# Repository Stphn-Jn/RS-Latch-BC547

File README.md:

R   S   Q   OUTPUT
0   0   0     0
1   0   0     1
1   1   0     0
0   1   0     0
0   0   0     0
1   1   1     0
0   1   1     0

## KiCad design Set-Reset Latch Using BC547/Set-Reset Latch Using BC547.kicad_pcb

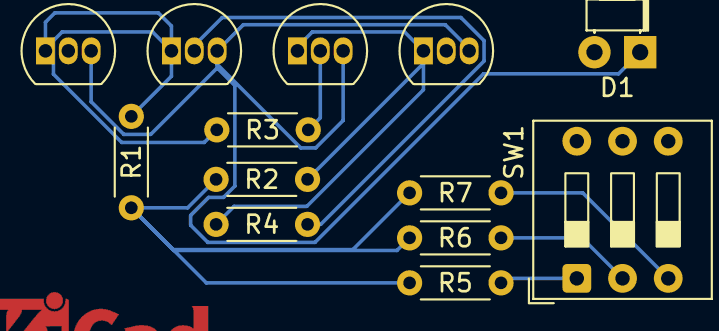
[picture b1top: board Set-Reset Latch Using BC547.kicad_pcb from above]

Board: 2 copper layers, 13 parts (0 on the bottom side), 11 nets.

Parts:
D1: LED; LED_D1.8mm_W1.8mm_H2.4mm_Horizontal_O1.27mm_Z4.9mm
Q1, Q2, Q3, Q4: BC547; TO-92_Inline
R1, R2, R3, R4, R5, R6, R7: 1K; R_Axial_DIN0204_L3.6mm_D1.6mm_P5.08mm_Horizontal
SW1: SW_DIP_x03; SW_DIP_SPSTx03_Slide_9.78x9.8mm_W7.62mm_P2.54mm

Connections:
+9V: R1.1, R2.1, R5.2, R6.2, R7.2
/Q: Q1.1 (C), Q2.1 (C), R1.2, R3.1, SW1.4
/R: Q1.2 (B), SW1.6
/S: Q4.2 (B), SW1.5
GND: D1.1 (K), Q1.3 (E), Q2.3 (E), Q3.3 (E), Q4.3 (E)
unnamed: D1.2 (A), Q3.1 (C), Q4.1 (C), R2.2, R4.1
unnamed: Q2.2 (B), R4.2
unnamed: Q3.2 (B), R3.2
unnamed: R5.1, SW1.1
unnamed: R6.1, SW1.2
unnamed: R7.1, SW1.3

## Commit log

2025-05-16 First KiCad File on my Repo
2025-05-16 README.md
